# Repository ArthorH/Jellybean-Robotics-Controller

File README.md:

# ESP8266 Multipurpose robotics controller 
 made from certified jellybean components!

## Project Status: **Finished**  
**Design** ✅ — **Fabrication** ✅ — **Assembly** ✅ — **Bringup** ✅ — **Testing** ✅  

## Key technologies:
&nbsp;&nbsp;&nbsp;&nbsp; &nbsp;&nbsp;&nbsp;&nbsp; &nbsp;&nbsp;&nbsp;&nbsp; &nbsp;&nbsp;&nbsp;&nbsp;

## Features
- Jelly Bean Components
- Universal footprints
- All usefull gpios has been broken out to connectors
- Additional I2C expander
- Battery voltage measurement
- Integrated easy to solder BMS module footprint (HW341)

## Jelly Bean components 
Board designed to allow manufacture of simple but capable wifi enabled robotics controller from most common avaliable components.

## Universal footprints
Board is designed to handle multiple packages of same components:

## Integrated BMS controller 
Integrated easy to solder BMS module footprint (HW341)

## Notice: BMS it needs to be bodged in order to work
This model of bms would not be used in future designs

# Use cases
## PCB mounted on simple mobile robot

## PCB used in a pneumatic controller during the robotic arena.

## License

MIT

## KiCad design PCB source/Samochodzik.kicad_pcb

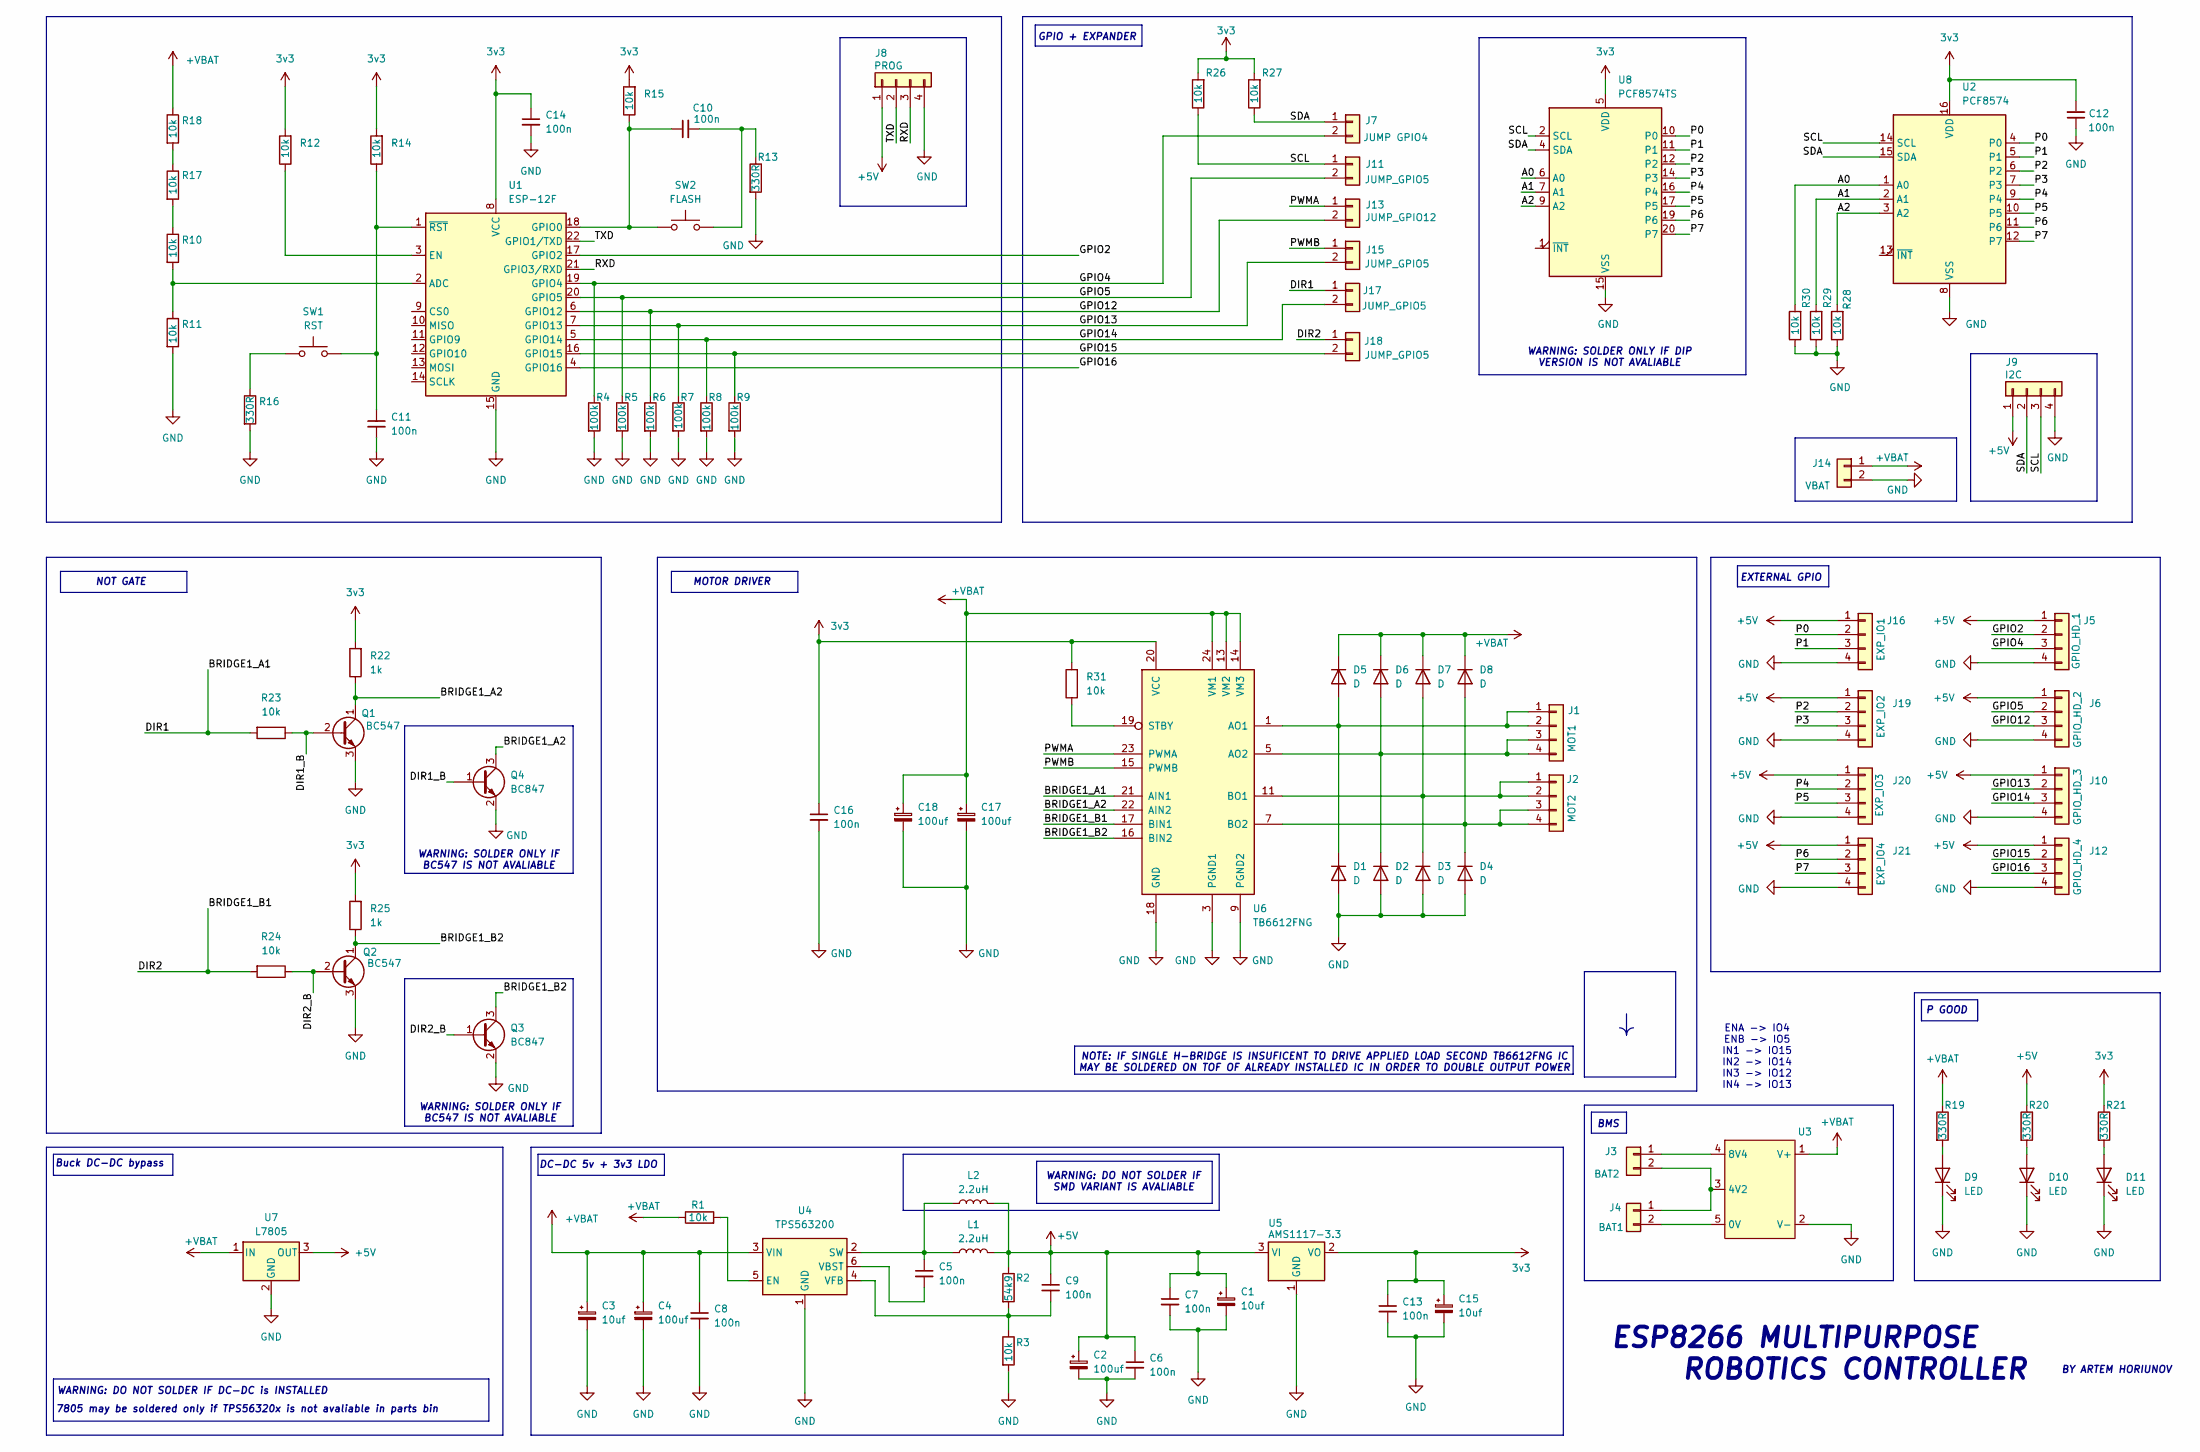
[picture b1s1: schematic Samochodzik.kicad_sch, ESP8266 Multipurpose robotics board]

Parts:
C1, C3, C15: 10uf; CP_EIA-7343-31_Kemet-D
C2, C4, C17, C18: 100uf; CP_Radial_D10.0mm_P2.50mm_P5.00mm
C5, C6, C7, C8, C9, C10, C11, C12, C13, C14, C16: 100n; C_0805_2012Metric_Pad1.18x1.45mm_HandSolder
D1, D2, D3, D4, D5, D6, D7, D8: D; D_DO-41_SOD81_P7.62mm_Horizontal
D9, D10, D11: LED; LED_D5.0mm
J1: MOT1; Molex_KK-254_AE-6410-04A_1x04_P2.54mm_Vertical
J2: MOT2; Molex_KK-254_AE-6410-04A_1x04_P2.54mm_Vertical
J3: BAT2; Molex_KK-254_AE-6410-02A_1x02_P2.54mm_Vertical
J4: BAT1; Molex_KK-254_AE-6410-02A_1x02_P2.54mm_Vertical
J5: GPIO_HD_1; Molex_KK-254_AE-6410-04A_1x04_P2.54mm_Vertical
J6: GPIO_HD_2; Molex_KK-254_AE-6410-04A_1x04_P2.54mm_Vertical
J7: JUMP GPIO4; PinHeader_1x02_P2.54mm_Vertical
J8: PROG; Molex_KK-254_AE-6410-04A_1x04_P2.54mm_Vertical
J9: I2C; Molex_KK-254_AE-6410-04A_1x04_P2.54mm_Vertical
J10: GPIO_HD_3; Molex_KK-254_AE-6410-04A_1x04_P2.54mm_Vertical
J11, J15, J17, J18: JUMP_GPIO5; PinHeader_1x02_P2.54mm_Vertical
J12: GPIO_HD_4; Molex_KK-254_AE-6410-04A_1x04_P2.54mm_Vertical
J13: JUMP_GPIO12; PinHeader_1x02_P2.54mm_Vertical
J14: VBAT; Molex_KK-254_AE-6410-02A_1x02_P2.54mm_Vertical
J16: EXP_IO1; Molex_KK-254_AE-6410-04A_1x04_P2.54mm_Vertical
J19: EXP_IO2; Molex_KK-254_AE-6410-04A_1x04_P2.54mm_Vertical
J20: EXP_IO3; Molex_KK-254_AE-6410-04A_1x04_P2.54mm_Vertical
J21: EXP_IO4; Molex_KK-254_AE-6410-04A_1x04_P2.54mm_Vertical
L1: 2.2uH; L_Sunlord_MWSA0624S
L2: 2.2uH; L_Radial_D7.5mm_P5.00mm_Fastron_07P
Q1, Q2: BC547; TO-92_Wide
Q3, Q4: BC847; SOT-23
R1, R3, R10, R11, R12, R14, R15, R17, R18, R23, R24, R26, R27, R28, R29, R30, R31: 10k; R_0603_1608Metric_Pad0.98x0.95mm_HandSolder
R2: 54k9; R_0603_1608Metric_Pad0.98x0.95mm_HandSolder
R4, R5, R6, R7, R8, R9: 100k; R_0603_1608Metric_Pad0.98x0.95mm_HandSolder
R13, R16, R19, R20, R21: 330R; R_0603_1608Metric_Pad0.98x0.95mm_HandSolder
R22: 1k; R_0603_1608Metric_Pad0.98x0.95mm_HandSolder
R25: 1k; R_0603_1608Metric
SW1: RST; SW_PUSH_6mm_H4.3mm
SW2: FLASH; SW_PUSH_6mm_H4.3mm
U1: ESP-12F; ESP-12E
U2: PCF8574; DIP-16_W10.16mm
U3: Chinese 20A BMS
U4: TPS563200; SOT-23-6
U5: AMS1117-3.3; SOT-223-3_TabPin2
U6: TB6612FNG; SSOP-24_5.3x8.2mm_P0.65mm
U7: L7805; TO-220-3_Horizontal_TabDown
U8: PCF8574TS; SSOP-20_4.4x6.5mm_P0.65mm

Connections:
3v3: C12.2, C13.1, C14.1, C15.1, C16.1, R12.2, R14.2, R15.2, R21.1, R22.2, R25.2, R26.2, R27.2, R31.2, U1.8 (VCC), U2.16 (VDD), U5.2 (VO), U6.20 (VCC), U8.5 (VDD)
+5V: C1.1, C2.1, C6.1, C7.1, C9.1, J5.1, J6.1, J8.1, J9.1, J10.1, J12.1, J16.1, J19.1, J20.1, J21.1, L1.2, L2.2, R2.1, R20.1, U5.3 (VI), U7.3 (OUT)
+VBAT: C3.1, C4.1, C8.1, C17.1, C18.1, D5.1 (K), D6.1 (K), D7.1 (K), D8.1 (K), J14.1, R1.1, R18.1, R19.1, U3.1 (V+), U4.3 (VIN), U6.13 (VM2), U6.14 (VM3), U6.24 (VM1), U7.1 (IN)
/A0: R30.2, U2.1 (A0), U8.6 (A0)
/A1: R29.2, U2.2 (A1), U8.7 (A1)
/A2: R28.2, U2.3 (A2), U8.9 (A2)
/BRIDGE1_A1: J17.1, R23.2, U6.21 (AIN1)
/BRIDGE1_A2: Q1.1 (C), Q4.3 (C), R22.1, U6.22 (AIN2)
/BRIDGE1_B1: J18.1, R24.2, U6.17 (BIN1)
/BRIDGE1_B2: Q2.1 (C), Q3.3 (C), R25.1, U6.16 (BIN2)
/DIR1_B: Q1.2 (B), Q4.1 (B), R23.1
/DIR2_B: Q2.2 (B), Q3.1 (B), R24.1
/GPIO2: J5.2, U1.17 (GPIO2)
/GPIO4: J5.3, J7.2, R4.1, U1.19 (GPIO4)
/GPIO5: J6.2, J11.2, R5.1, U1.20 (GPIO5)
/GPIO12: J6.3, J13.2, R6.1, U1.6 (GPIO12)
/GPIO13: J10.2, J15.2, R7.1, U1.7 (GPIO13)
/GPIO14: J10.3, J17.2, R8.1, U1.5 (GPIO14)
/GPIO15: J12.2, J18.2, R9.1, U1.16 (GPIO15)
/GPIO16: J12.3, U1.4 (GPIO16)
/P0: J16.2, U2.4 (P0), U8.10 (P0)
/P1: J16.3, U2.5 (P1), U8.11 (P1)
/P2: J19.2, U2.6 (P2), U8.12 (P2)
/P3: J19.3, U2.7 (P3), U8.14 (P3)
/P4: J20.2, U2.9 (P4), U8.16 (P4)
/P5: J20.3, U2.10 (P5), U8.17 (P5)
/P6: J21.2, U2.11 (P6), U8.19 (P6)
/P7: J21.3, U2.12 (P7), U8.20 (P7)
/PWMA: J13.1, U6.23 (PWMA)
/PWMB: J15.1, U6.15 (PWMB)
/RXD: J8.3, U1.21 (GPIO3/RXD)
/SCL: J9.3, J11.1, R26.1, U2.14 (SCL), U8.2 (SCL)
/SDA: J7.1, J9.2, R27.1, U2.15 (SDA), U8.4 (SDA)
/TXD: J8.2, U1.22 (GPIO1/TXD)
GND: C1.2, C2.2, C3.2, C4.2, C6.2, C7.2, C8.2, C11.2, C12.1, C13.2, C14.2, C15.2, C16.2, C17.2, C18.2, D1.2 (A), D2.2 (A), D3.2 (A), D4.2 (A), D9.1 (K), D10.1 (K), D11.1 (K), J5.4, J6.4, J8.4, J9.4, J10.4, J12.4, J14.2, J16.4, J19.4, J20.4, J21.4, Q1.3 (E), Q2.3 (E), Q3.2 (E), Q4.2 (E), R3.2, R4.2, R5.2, R6.2, R7.2, R8.2, R9.2, R11.2, R13.2, R16.2, R28.1, R29.1, R30.1, U1.15 (GND), U2.8 (VSS), U3.2 (V-), U4.1 (GND), U5.1 (GND), U6.3 (PGND1), U6.4 (PGND1), U6.9 (PGND2), U6.10 (PGND2), U6.18 (GND), U7.2 (GND), U8.15 (VSS)
unnamed: C10.2, R13.1, SW2.2
unnamed: D1.1 (K), D5.2 (A), J1.1, J1.2, U6.1 (AO1), U6.2 (AO1)
unnamed: D2.1 (K), D6.2 (A), J1.3, J1.4, U6.5 (AO2), U6.6 (AO2)
unnamed: D3.1 (K), D7.2 (A), J2.1, J2.2, U6.11 (BO1), U6.12 (BO1)
unnamed: D4.1 (K), D8.2 (A), J2.3, J2.4, U6.7 (BO2), U6.8 (BO2)
unnamed: D9.2 (A), R19.2
unnamed: D10.2 (A), R20.2
unnamed: D11.2 (A), R21.2
unnamed: J3.1, U3.4 (8V4)
unnamed: J3.2, J4.1, U3.3 (4V2)
unnamed: J4.2, U3.5 (0V)
unnamed: R10.1, R17.2
unnamed: R16.1, SW1.1
unnamed: R17.1, R18.2
unnamed: R10.2, R11.1, U1.2 (ADC)
unnamed: R12.1, U1.3 (EN)
unnamed: C10.1, R15.1, SW2.1, U1.18 (GPIO0)
unnamed: C11.1, R14.1, SW1.2, U1.1 (~RST)
unnamed: R1.2, U4.5 (EN)
unnamed: C5.1, L1.1, L2.1, U4.2 (SW)
unnamed: C5.2, U4.6 (VBST)
unnamed: C9.2, R2.2, R3.1, U4.4 (VFB)
unnamed: R31.1, U6.19 (STBY)

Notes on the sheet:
BY ARTEM HORIUNOV
BMS
NOT GATE
WARNING: SOLDER ONLY IF BC547 IS NOT AVALIABLE
WARNING: DO NOT SOLDER IF SMD VARIANT IS AVALIABLE
WARNING: DO NOT SOLDER IF DC-DC is INSTALLED
ESP8266 MULTIPURPOSE ROBOTICS CONTROLLER
P GOOD
MOTOR DRIVER
NOTE: IF SINGLE H-BRIDGE IS INSUFICENT TO DRIVE APPLIED LOAD SECOND TB6612FNG IC MAY BE SOLDERED ON TOF OF ALREADY INSTALLED IC IN ORDER TO DOUBLE OUTPUT POWER
Buck DC-DC bypass
GPIO + EXPANDER
ENA -> IO4 ENB -> IO5 IN1 -> IO15 IN2 -> IO14 IN3 -> IO12 IN4 -> IO13
DC-DC 5v + 3v3 LDO
WARNING: SOLDER ONLY IF DIP VERSION IS NOT AVALIABLE
7805 may be soldered only if TPS56320x is not avaliable in parts bin
EXTERNAL GPIO

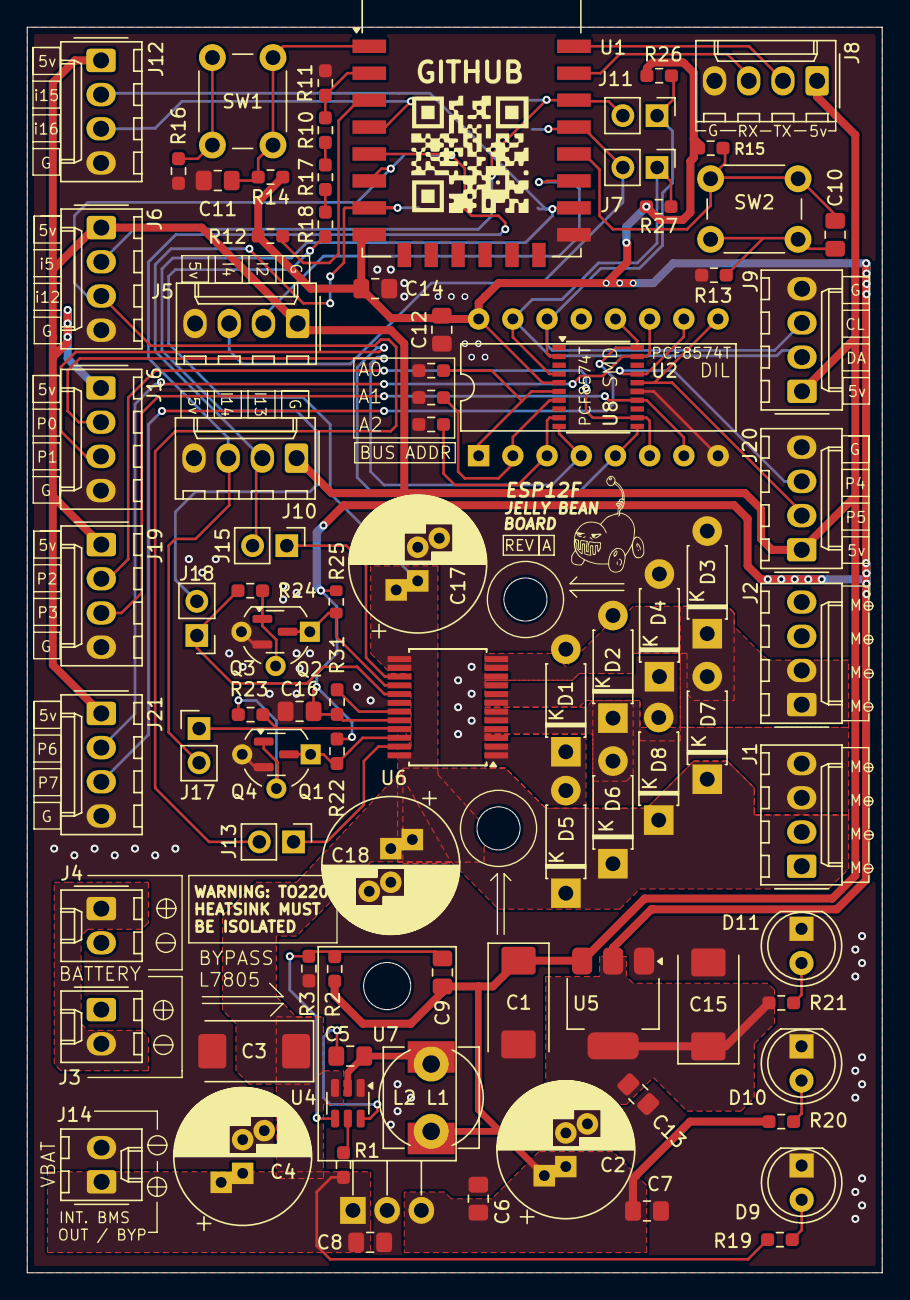
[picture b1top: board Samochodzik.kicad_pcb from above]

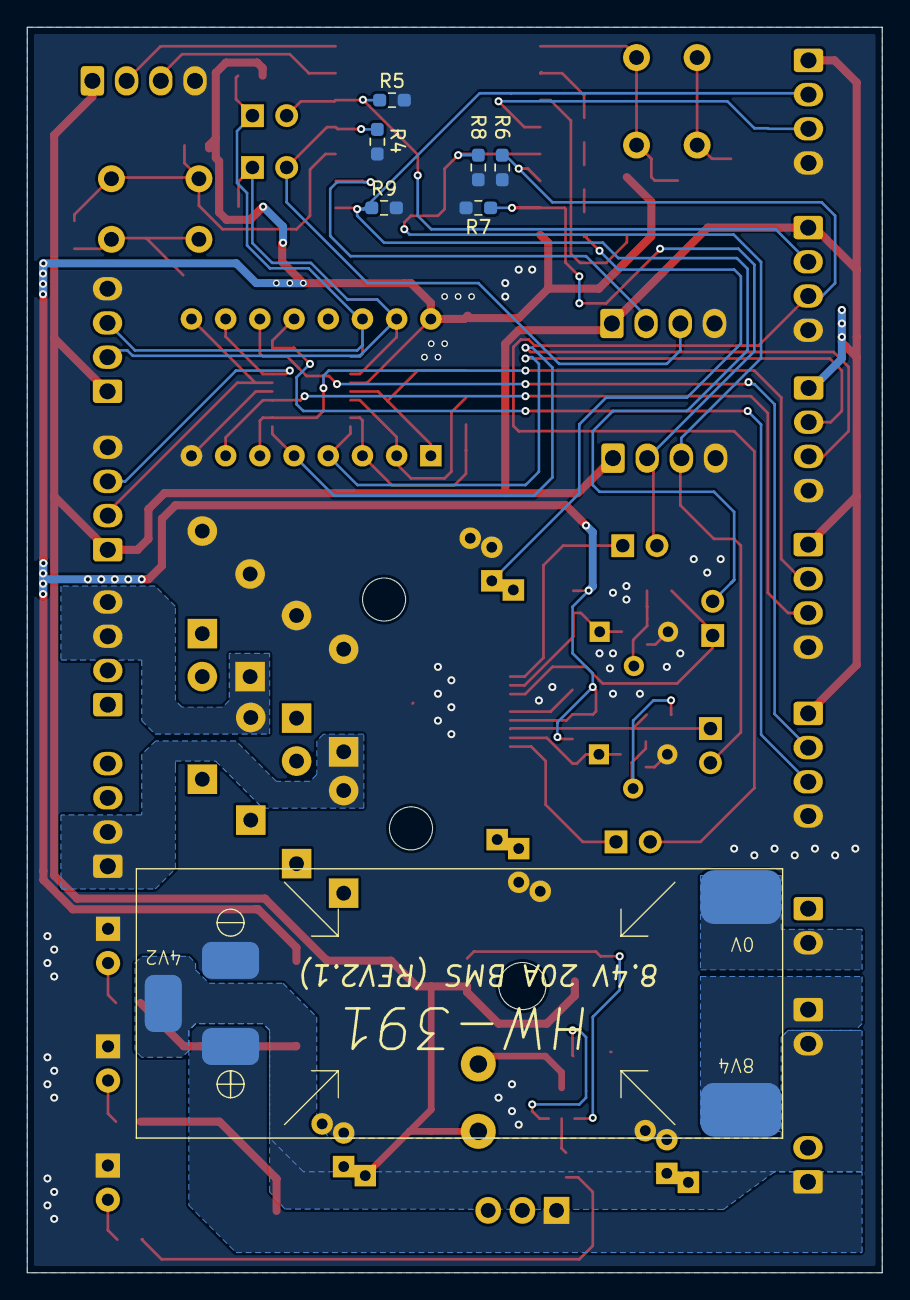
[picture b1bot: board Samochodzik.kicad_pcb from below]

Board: 2 copper layers, 63.5 x 92.5 mm, 99 parts (7 on the bottom side), 58 nets.

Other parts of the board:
H1, H2: MountingHole; MountingHole_3.2mm_M3_DIN965

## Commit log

2024-03-12 Create README.md
    Edited readme
2024-03-12 DRC errors corrected
2024-03-13 Update README.md
    Added fabrication file render
2024-07-10 Update README.md
    Typo and MD fix
2025-02-14 Do cleanup
